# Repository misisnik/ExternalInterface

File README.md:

External user irnterface with usb
===================================
Project tags:
  - MCP2210
  - Displat with "IST3020"
  - Joystick
  - Python library

Project tree:
- hw
  - board with buttons on the left side - KiCad files - schematics and pcb
  - board with buttons next to joystick - KiCad files - schematics and pcb
  - casing - FreeCad projects for casing this user interface (3D pronting)
- sw
  - Python 3.4 project lib

It contains:
- [SW lib.](https://github.com/misisnik/ExternalInterface/tree/master/sw)
- [HW board 1](https://github.com/misisnik/ExternalInterface/tree/master/hw/board_buttons_next_to_joystick)
- [HW board 2](https://github.com/misisnik/ExternalInterface/tree/master/hw/board_buttons_on_the_other_side)
- [HW 3D casing](https://github.com/misisnik/ExternalInterface/tree/master/hw/casing)

Installation
------------
	-Ubuntu and python 2.7
	---------------
			$ apt-get update
			$ apt-get install python-dev
			$ apt-get install cython
			$ apt-get install libusb-1.0.0 libusb-1.0.0-dev libudev-dev
			$ pip install hidapi

		install Pillow
			$ apt-get install libjpeg-dev
			$ pip3 install pillow

		-- display LIB
		git clone https://github.com/misisnik/ExternalInterface

	-Raspbian Jesee
	---------------
			$ apt-get update
			$ sudo apt-get install git python3.4 python3-dev

		install pip3 from git
			$ git clone https://github.com/pypa/pip
			$ cd pip
			$ python3.4 setup.py install
			$ cd ..
			$ rm -r pip

		install cython
			$ apt-get install cython3

		libusb
			$ apt-get install libusb-1.0.0 libusb-1.0.0-dev libudev-dev

		install cython-hidapi
			$ git clone https://github.com/gbishop/cython-hidapi.git
			$ cd cython-hidapi
			$ python3 setup.py build
			$ python3 setup.py install
			$ cd ..
			$ rm -r cython-hidapi

		install Pillow
			$ apt-get install libjpeg-dev
			$ pip3 install pillow

		-- display LIB
		git clone https://github.com/misisnik/ExternalInterface

Examples
---------------

-[Main example - introduction of display + snake game](https://github.com/misisnik/ExternalInterface/blob/master/sw/example.py)

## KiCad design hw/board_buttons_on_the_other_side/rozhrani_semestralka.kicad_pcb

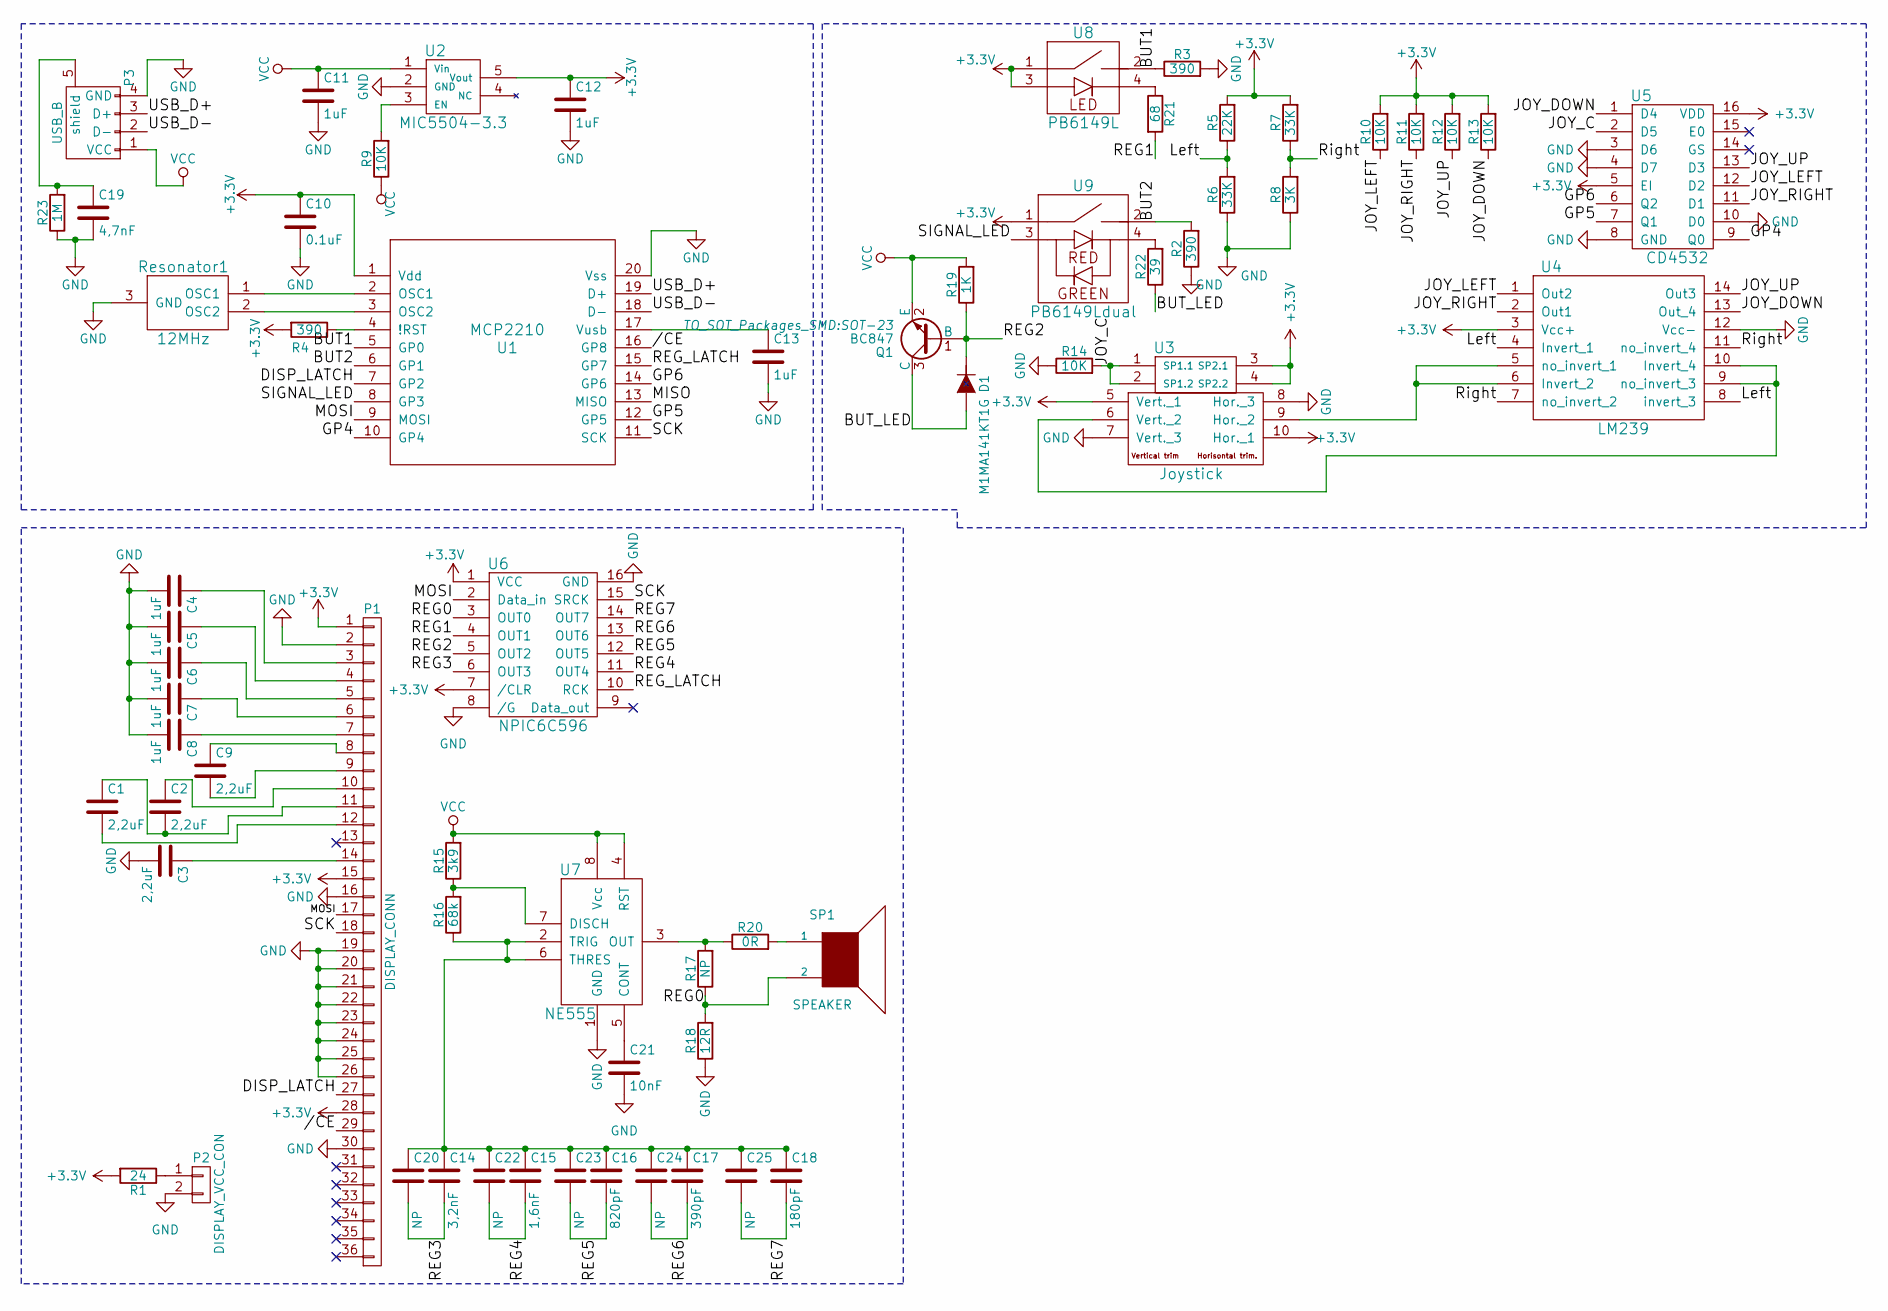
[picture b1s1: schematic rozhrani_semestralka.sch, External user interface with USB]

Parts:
C1, C2, C3, C9: 2,2uF; C_0603_HandSoldering
C4, C5, C6, C7, C8, C11, C12, C13: 1uF; C_0603_HandSoldering
C10: 0.1uF; C_0603_HandSoldering
C14: 3,2nF; C_0603_HandSoldering
C15: 1,6nF; C_0603_HandSoldering
C16: 820pF; C_0603_HandSoldering
C17: 390pF; C_0603_HandSoldering
C18: 180pF; C_0603_HandSoldering
C19: 4,7nF; C_0603_HandSoldering
C20, C22, C23, C24, C25: NP; C_0603_HandSoldering
C21: 10nF; C_0603_HandSoldering
D1: M1MA141KT1G; SOT-323
P1: DISPLAY_CONN; ZIF36
P2: DISPLAY_VCC_CON; disp_nap
P3: USB_B
Q1: BC847; SOT-23
R1: 24; R_0603_HandSoldering
R2, R3, R4: 390; R_0603_HandSoldering
R5: 22K; R_0603_HandSoldering
R6, R7: 33K; R_0603_HandSoldering
R8: 3K; R_0603_HandSoldering
R9, R10, R11, R12, R13, R14: 10K; R_0603_HandSoldering
R15: 3k9; R_0603_HandSoldering
R16: 68k; R_0603_HandSoldering
R17: NP; R_0603_HandSoldering
R18: 12R; R_0603_HandSoldering
R19: 1K; R_0603_HandSoldering
R20: 0R; R_0603_HandSoldering
R21: 68; R_0603_HandSoldering
R22: 39; R_0603_HandSoldering
R23: 1M; R_0603_HandSoldering
Resonator1: 12MHz; resonator12MHz
SP1: SPEAKER; Buzzer
U1: MCP2210; SOIC-20_7.5x12.8mm_Pitch1.27mm
U2: MIC5504-3.3; SOT-23-5
U3: Joystick
U4: LM239; SOIC-14_3.9x8.7mm_Pitch1.27mm
U5: CD4532; SOIC-16_3.9x9.9mm_Pitch1.27mm
U6: NPIC6C596; SOIC-16_3.9x9.9mm_Pitch1.27mm
U7: NE555; SOIC-8_3.9x4.9mm_Pitch1.27mm
U8: PB6149L
U9: PB6149Ldual; PB6149L

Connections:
+3V3: C10.1, C12.1, P1.1, P1.15, P1.28, R1.2, R4.2, R5.2, R7.2, R10.2, R11.2, R12.2, R13.2, U1.1 (Vdd), U2.5 (Vout), U3.3 (SP2.1), U3.4 (SP2.2), U3.5 (Vert._1), U3.10 (Hor._1), U4.3 (Vcc+), U5.5 (EI), U5.16 (VDD), U6.1 (VCC), U6.7 (/CLR), U8.1, U8.3, U9.1
//CE: P1.29, U1.16 (GP8)
/BUT1: R3.1, U1.5 (GP0), U8.2
/BUT2: R2.2, U1.6 (GP1), U9.2
/BUT_LED: D1.1 (A), Q1.3 (C), R22.1
/DISP_LATCH: P1.27, U1.7 (GP2)
/GP4: U1.10 (GP4), U5.9 (Q0)
/GP5: U1.12 (GP5), U5.7 (Q1)
/GP6: U1.14 (GP6), U5.6 (Q2)
/JOY_C: R14.2, U3.1 (SP1.1), U3.2 (SP1.2), U5.2 (D5)
/JOY_DOWN: R13.1, U4.13 (Out_4), U5.1 (D4)
/JOY_LEFT: R10.1, U4.1 (Out2), U5.12 (D2)
/JOY_RIGHT: R11.1, U4.2 (Out1), U5.11 (D1)
/JOY_UP: R12.1, U4.14 (Out3), U5.13 (D3)
/Left: R5.1, R6.2, U4.4 (Invert_1), U4.8 (invert_3)
/MISO: U1.13 (MISO)
/MOSI: P1.17, U1.9 (MOSI), U6.2 (Data_in)
/REG0: R17.1, R18.2, SP1.2, U6.3 (OUT0)
/REG1: R21.2, U6.4 (OUT1)
/REG2: D1.3 (K), Q1.1 (B), R19.1, U6.5 (OUT2)
/REG3: C14.2, C20.2, U6.6 (OUT3)
/REG4: C15.2, C22.2, U6.11 (OUT4)
/REG5: C16.2, C23.2, U6.12 (OUT5)
/REG6: C17.2, C24.2, U6.13 (OUT6)
/REG7: C18.2, C25.2, U6.14 (OUT7)
/REG_LATCH: U1.15 (GP7), U6.10 (RCK)
/Right: R7.1, R8.2, U4.7 (no_invert_2), U4.11 (no_invert_4)
/SCK: P1.18, U1.11 (SCK), U6.15 (SRCK)
/SIGNAL_LED: U1.8 (GP3), U9.3
/USB_D+: P3.3 (D+), U1.19 (D+)
/USB_D-: P3.2 (D-), U1.18 (D-)
GND: C3.2, C4.2, C5.2, C6.2, C7.2, C8.2, C10.2, C11.2, C12.2, C13.2, C19.2, C21.2, P1.2, P1.16, P1.19, P1.20, P1.21, P1.22, P1.23, P1.24, P1.25, P1.26, P1.30, P2.2, P3.4 (GND), R2.1, R3.2, R6.1, R8.1, R14.1, R18.1, R23.1, Resonator1.3 (GND), U1.20 (Vss), U2.2 (GND), U3.7 (Vert._3), U3.8 (Hor._3), U4.12 (Vcc-), U5.3 (D6), U5.4 (D7), U5.8 (GND), U5.10 (D0), U6.8 (/G), U6.16 (GND), U7.1 (GND); also elsewhere on the board
unnamed: C1.1, C2.2, P1.11
unnamed: C1.2, P1.12
unnamed: C2.1, P1.10
unnamed: C3.1, P1.14
unnamed: C4.1, P1.3
unnamed: C5.1, P1.4
unnamed: C6.1, P1.5
unnamed: C7.1, P1.6
unnamed: C8.1, P1.7
unnamed: C9.1, P1.8
unnamed: C9.2, P1.9
unnamed: C13.1, U1.17 (Vusb)
unnamed: C14.1, C15.1, C16.1, C17.1, C18.1, C20.1, C22.1, C23.1, C24.1, C25.1, R16.1, U7.2 (TRIG), U7.6 (THRES)
unnamed: C19.1, P3.5 (shield), R23.2
unnamed: C21.1, U7.5 (CONT)
unnamed: P2.1, R1.1
unnamed: R4.1, U1.4 (!RST)
unnamed: R9.2, U2.3 (EN)
unnamed: R15.1, R16.2, U7.7 (DISCH)
unnamed: R17.2, R20.1, U7.3 (OUT)
unnamed: R20.2, SP1.1
unnamed: R21.1, U8.4
unnamed: R22.2, U9.4
unnamed 63: Resonator1.1 (OSC1), U1.2 (OSC1); also elsewhere on the board
unnamed 64: Resonator1.2 (OSC2), U1.3 (OSC2); also elsewhere on the board
unnamed: U3.6 (Vert._2), U4.9 (no_invert_3), U4.10 (Invert_4)
unnamed: U3.9 (Hor._2), U4.5 (no_invert_1), U4.6 (Invert_2)
VCC: C11.1, P3.1 (VCC), Q1.2 (E), R9.1, R15.2, R19.2, U2.1 (Vin), U7.4 (RST), U7.8 (Vcc)

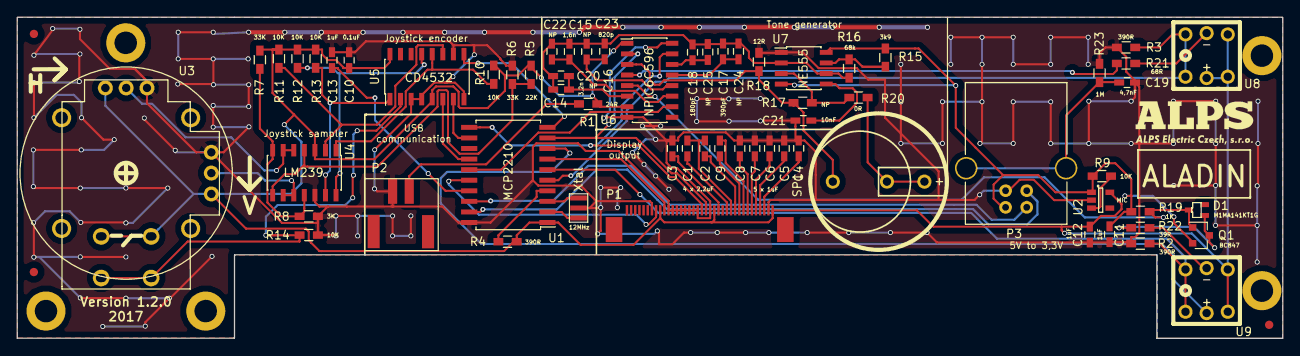
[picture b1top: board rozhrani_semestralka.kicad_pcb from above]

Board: 2 copper layers, 152.0 x 38.6 mm, 67 parts (0 on the bottom side), 59 nets.

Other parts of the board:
FID1, FID2, FID3**: Fiducial_1mm_Dia_2.54mm_Outer_CopperTop
Xtal: 12MHz; resonator12MHz

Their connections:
GND: Xtal.3; also elsewhere on the board
unnamed 63: Xtal.1; also elsewhere on the board
unnamed 64: Xtal.2; also elsewhere on the board

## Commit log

2016-04-04 First commit - create project repository
2016-04-04 Reverse display function
2016-04-06 Setup demo and repaired bugs and mistakes...
2016-04-06 Position of one line text - align
2016-04-06 Added rules for creating text in multiline function - when is new line?
2016-04-06 Update positioning of multiline lext - align again
2016-04-06 reverse mode updated
2016-04-06 Window rotation added
2016-04-06 Small protection when plug off usb and plug in
2016-04-06 Added joystick communication + menu component also added
2016-04-06 Added exception to unconected USB - after connect then continue to working
2016-04-06 cleaning code and added some function into Display class
2016-04-06 Prepare main class Display - now can someone juts know only this class to woork with display - also rework menu
2016-04-08 Add bom to HW part, create function textArea for big texts
2016-04-08 Upgrade value of resitors neer to joystick + added bom
2016-04-08 Setup new board - changed from test board configuration
2016-04-08 Select number -> from range by step
2016-04-08 Error LED diode function
2016-04-11 choose number reapired
2016-04-11 Added checkbox and Question except control via buttons OK and NG
2016-04-11 Change holes to another buttons
2016-04-11 Sorting schematic parts
2016-04-12 just updated schematic package in NPIC6C596
2016-04-13 Creating windows on display
2016-04-13 Prepare lib for MatrixOrbital suport
2016-04-13 Select number added function for increment and decrement 10
2016-04-13 Text area add controll via left and right side of joystick
2016-04-20 Added buttons - OK and NG
2016-04-20 Added buttons light - LED under buttons OK and NG
2016-04-20 Add sound controll
2016-04-22 Updated rewriting bitmap, might be faster
2016-04-22 Added new NumberChoose and add parametre to text array
2016-04-22 Added circle and rectangle loader
2016-04-22 Add quantity widget
2016-04-25 Added hw board version 1.0.0 - buttons to another side and small updates
2016-04-29 missing disable underlight of buttons
2016-04-29 added fonts
2016-04-29 Added function for rendering images also added small icons
2016-04-29 The device support of linux distribution
2016-05-11 Separate two different PCB - just 2 KiCad projects - buttons on left side or buttons next to joystick
2016-05-11 Added icons 16x16 and 32x32
2016-05-11 Added license file
2016-05-11 Readme eddited
2016-05-11 Deleted old files
2016-05-11 Added license header to each lib. file
2016-05-11 Updated display bom
2016-05-11 Reduced board size and replace mounting holes + indication LED
2016-05-11 first revision of caseing
2016-05-12 Just remove one mounting hole
2016-05-12 Added company logo + dimensions - board 1.0.0B
2016-05-13 Caseing revise
2016-05-13 Repaired mistakes
2016-05-13 added instalation instruction for Raspbian Jesee
2016-05-16 Added relative path to icon list show
2016-05-25 added capacitor value to buzzer
2016-05-26 demo added - snake and so on
2016-05-28 Added fonts path
2016-05-28 repaire font error
2016-05-28 Big font renamed
2016-05-28 Rename files
2016-05-28 Created examples
2016-05-28 some foo
2016-05-28 Import edited
2016-05-28 Just added if is windows...
2016-05-28 Just sorting whole repository
2016-05-28 Edit values of capacitors near tone generator + updated BOM + rename casing folder
2016-05-29 Updated bom
2016-05-29 Just generate some files
2016-06-20 unconnected central button
2016-06-20 Remove delay of register and add orientation for joystick
2016-08-10 Just created casing for version 2
2016-08-29 newer version added
2016-09-21 edit demo
2016-09-22 created version 1.1.0 -- usb connector rotated -- there is no compatible with printed casing, please use version 1.0.0B
2016-10-16 Eddited board to version 1.1.1 - now one of button has choise for 2 colour also added values to silk screen
2017-01-12 Aladin v 1.2.0 pcb - repaired GPIO for /CE and also BUZZERs capacitors, some footprints had change
2017-01-13 Just added fiducials for stencil.
2022-11-20 Adding tarfile member sanitization to extractall()
